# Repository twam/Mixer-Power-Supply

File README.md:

Mixer-Power-Supply
===

This repository is part of the USB audio mixer project described on https://www.twam.info/general/building-a-custom-usb-audio-mixer.

## License

[![CC BY-SA 4.0][cc-by-sa-shield]][cc-by-sa]

This work is licensed under a [Creative Commons Attribution-NonCommercial-ShareAlike 4.0 International License][cc-by-sa].

[![CC BY-SA 4.0][cc-by-sa-image]][cc-by-sa]

[cc-by-sa]: http://creativecommons.org/licenses/by-nc-sa/4.0/
[cc-by-sa-image]: https://licensebuttons.net/l/by-nc-sa/4.0/88x31.png
[cc-by-sa-shield]: https://img.shields.io/badge/License-CC%20BY--NC--SA%204.0-lightgrey.svg

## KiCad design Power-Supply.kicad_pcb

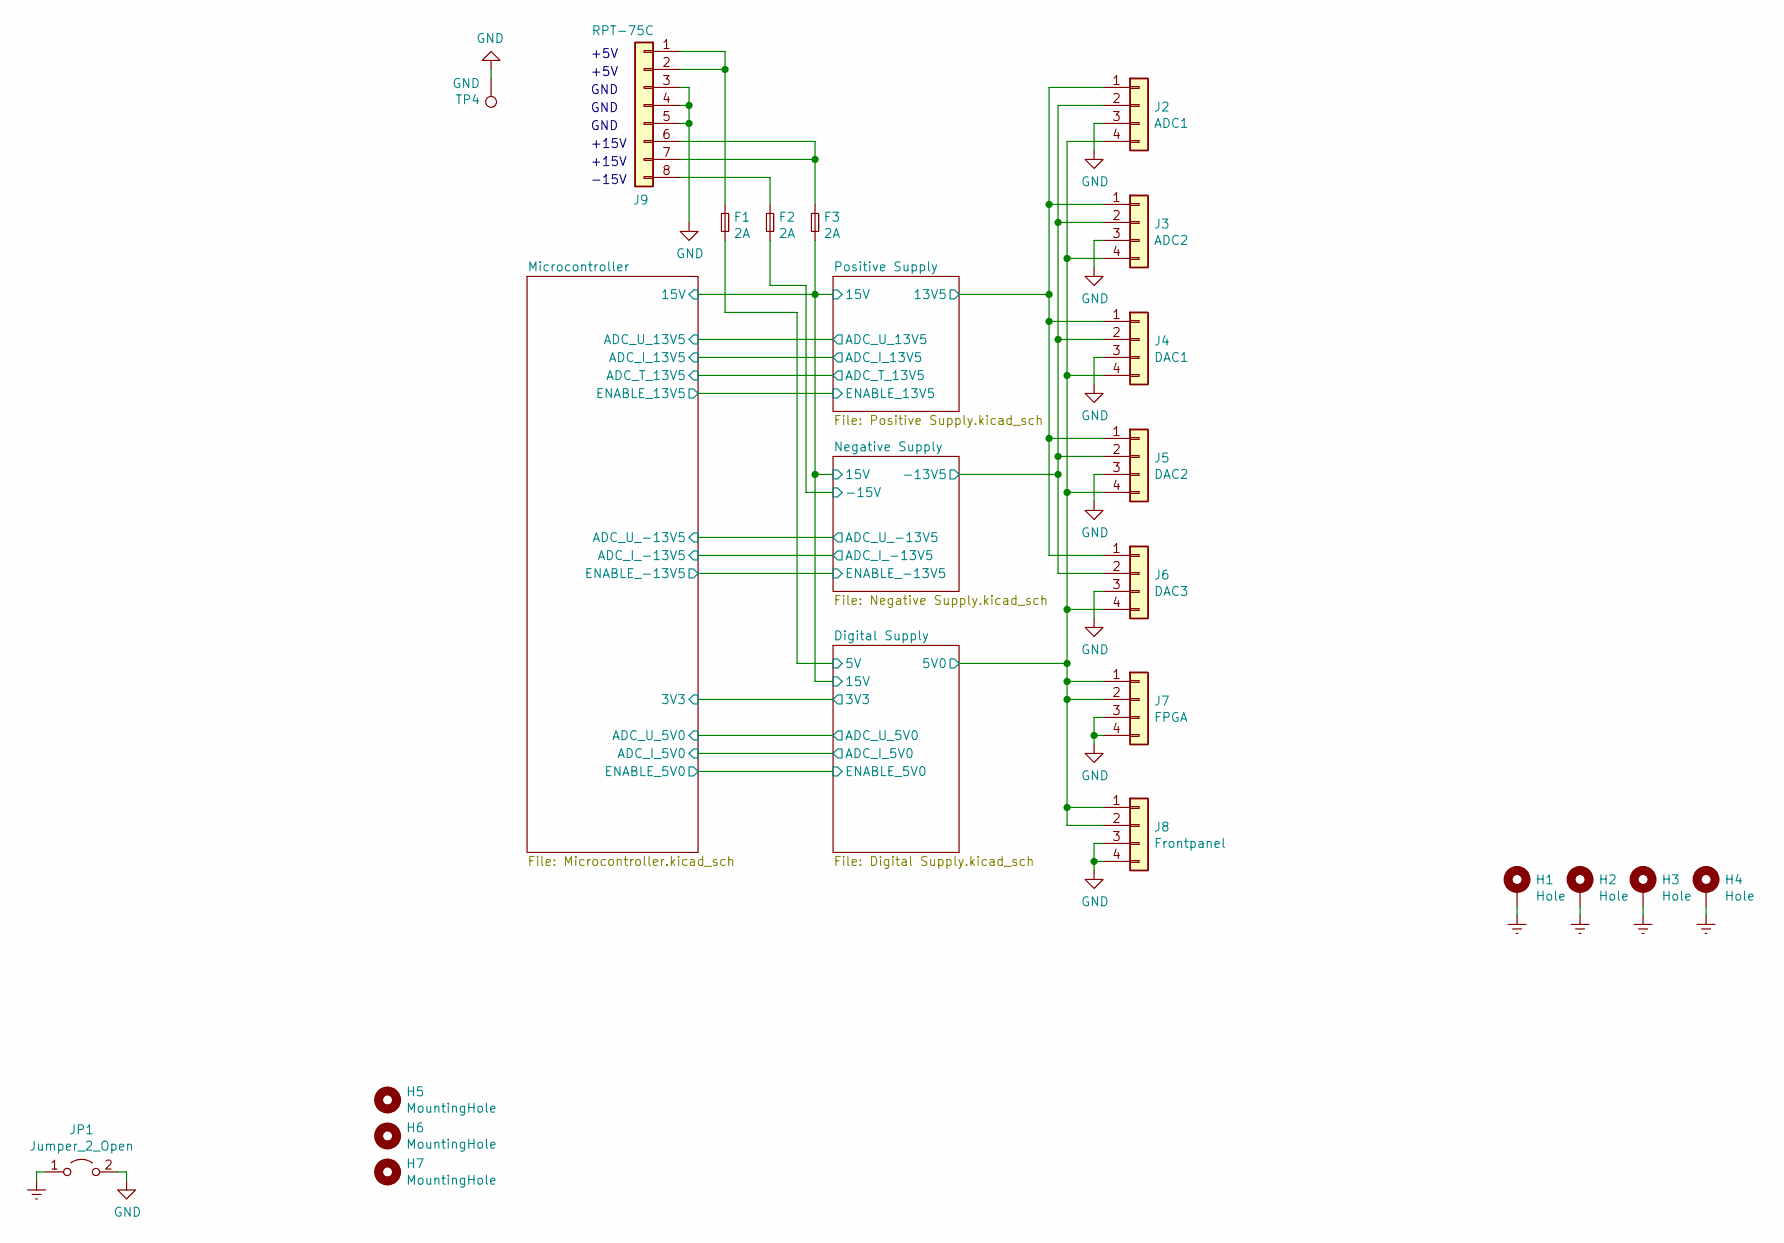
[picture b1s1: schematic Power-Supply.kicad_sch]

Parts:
F1, F2, F3: 2A; Fuse_0603_1608Metric_Pad1.05x0.95mm_HandSolder; LCSC C187605
H1, H2, H3, H4: Hole; MountingHole_3.2mm_M3_DIN965_Pad
H5, H6, H7: MountingHole; MountingHole_JLCPCB
J2: ADC1; JST_VH_B4P-VH_1x04_P3.96mm_Vertical
J3: ADC2; JST_VH_B4P-VH_1x04_P3.96mm_Vertical
J4: DAC1; JST_VH_B4P-VH_1x04_P3.96mm_Vertical
J5: DAC2; JST_VH_B4P-VH_1x04_P3.96mm_Vertical
J6: DAC3; JST_VH_B4P-VH_1x04_P3.96mm_Vertical
J7: FPGA; JST_VH_B4P-VH_1x04_P3.96mm_Vertical
J8: Frontpanel; JST_VH_B4P-VH_1x04_P3.96mm_Vertical
J9: RPT-75C; JST_VH_B8P-VH_1x08_P3.96mm_Vertical
JP1: Jumper_2_Open; SolderJumper-2_P1.3mm_Open_RoundedPad1.0x1.5mm
TP4: GND; TestPoint_Pad_D2.0mm

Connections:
/Digital Supply/5V: F1.1; also elsewhere on the board
/Digital Supply/5V0: J2.4, J3.4, J4.4, J5.4, J6.4, J7.1, J7.2, J8.1, J8.2; also elsewhere on the board
/Digital Supply/15V: F3.1; also elsewhere on the board
/Negative Supply/-13V5: J2.2, J3.2, J4.2, J5.2, J6.2; also elsewhere on the board
/Negative Supply/-15V: F2.1; also elsewhere on the board
/Positive Supply/13V5: J2.1, J3.1, J4.1, J5.1, J6.1; also elsewhere on the board
Earth: H1.1, H2.1, H3.1, H4.1, JP1.1 (A)
GND: J2.3, J3.3, J4.3, J5.3, J6.3, J7.3, J7.4, J8.3, J8.4, J9.3, J9.4, J9.5, JP1.2 (B), TP4.1; also elsewhere on the board
unnamed: F1.2, J9.1, J9.2
unnamed: F2.2, J9.8
unnamed: F3.2, J9.6, J9.7

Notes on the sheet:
+5V
GND
-15V
+15V

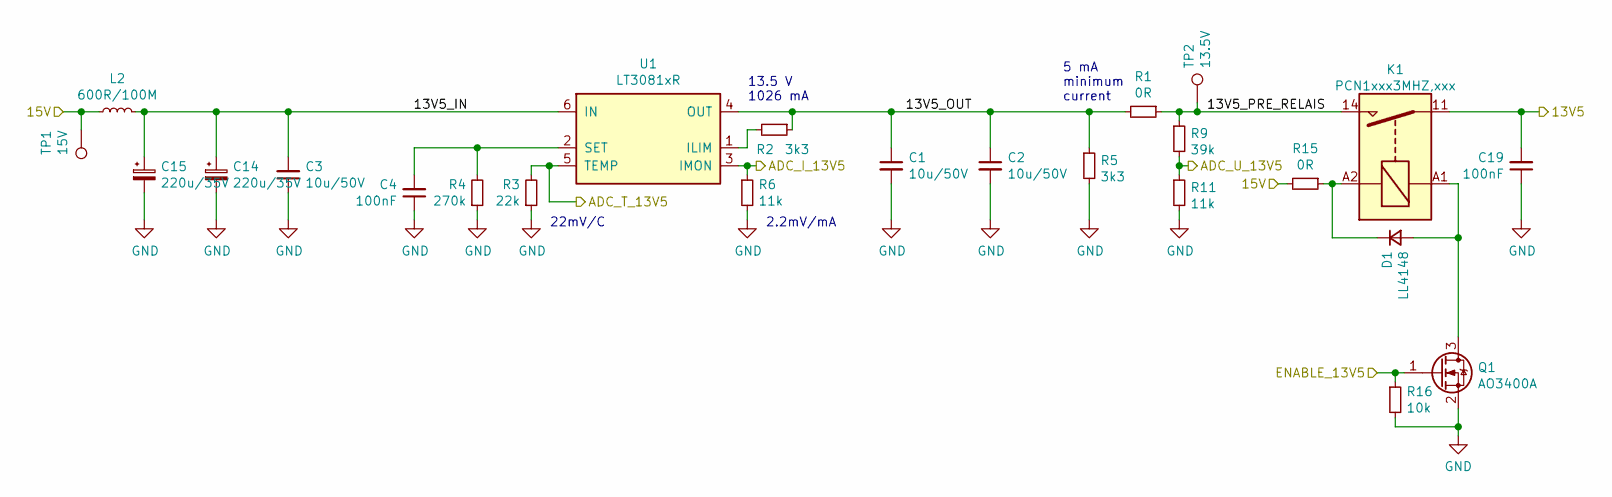
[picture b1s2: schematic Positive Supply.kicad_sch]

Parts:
C1, C2, C3: 10u/50V; C_1206_3216Metric; LCSC C13585
C4, C19: 100nF; C_0805_2012Metric; LCSC C49678
C14, C15: 220u/35V; CP_Radial_D8.0mm_P3.50mm; LCSC C201212
D1: LL4148; D_MiniMELF; LCSC C9808
K1: PCN1xxx3MHZ,xxx
L2: 600R/100M; L_0805_2012Metric; LCSC C1017
Q1: AO3400A; TSOT-23; LCSC C20917
R1, R15: 0R; R_0805_2012Metric; LCSC C17477
R2, R5: 3k3; R_0805_2012Metric; LCSC C26010
R3: 22k; R_0805_2012Metric; LCSC C17560
R4: 270k; R_0805_2012Metric; LCSC C17589
R6, R11: 11k; R_0805_2012Metric; LCSC C17429
R9: 39k; R_0805_2012Metric; LCSC C25826
R16: 10k; R_0805_2012Metric; LCSC C17414
TP1: 15V; TestPoint_Pad_D2.0mm
TP2: 13.5V; TestPoint_Pad_D2.0mm
U1: LT3081xR; TO-220-7_P2.54x3.8mm_StaggerOdd_Lead5.85mm_TabDown

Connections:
/Digital Supply/15V: L2.1, R15.2, TP1.1; also elsewhere on the board
/Microcontroller/ADC_I_13V5: R6.1, U1.3 (IMON); also elsewhere on the board
/Microcontroller/ADC_T_13V5: R3.2, U1.5 (TEMP); also elsewhere on the board
/Microcontroller/ADC_U_13V5: R9.2, R11.1; also elsewhere on the board
/Microcontroller/ENABLE_13V5: Q1.1 (G), R16.1; also elsewhere on the board
/Positive Supply/13V5: C19.2, K1.11; also elsewhere on the board
/Positive Supply/13V5_IN: C3.2, C14.1, C15.1, L2.2, U1.6 (IN)
/Positive Supply/13V5_OUT: C1.1, C2.1, R1.2, R2.1, R5.1, U1.4 (OUT)
/Positive Supply/13V5_PRE_RELAIS: K1.14, R1.1, R9.1, TP2.1
GND: C1.2, C2.2, C3.1, C4.1, C14.2, C15.2, C19.1, Q1.2 (S), R3.1, R4.1, R5.2, R6.2, R11.2, R16.2; also elsewhere on the board
unnamed: C4.2, R4.2, U1.2 (SET)
unnamed: D1.1 (K), K1.A2, R15.1
unnamed: D1.2 (A), K1.A1, Q1.3 (D)
unnamed: R2.2, U1.1 (ILIM)

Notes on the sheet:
2.2mV/mA
5 mA minimum current
22mV/C
13.5 V 1026 mA

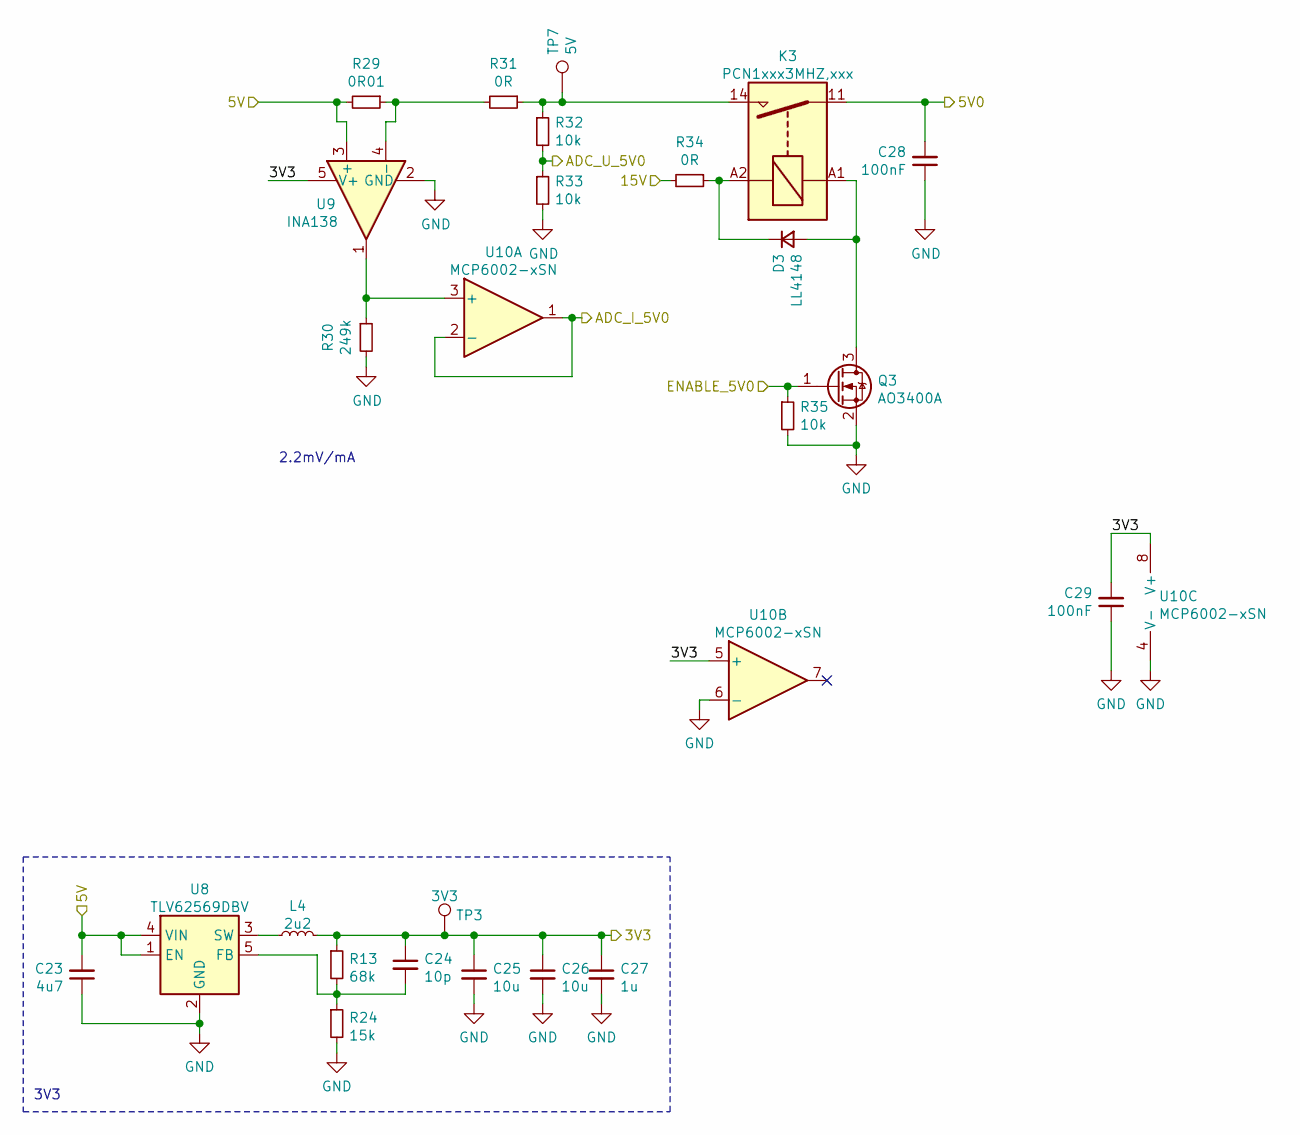
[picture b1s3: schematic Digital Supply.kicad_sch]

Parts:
C23: 4u7; C_0805_2012Metric; LCSC C1779
C24: 10p; C_0805_2012Metric; LCSC C1785
C25, C26: 10u; C_0805_2012Metric; LCSC C15850
C27: 1u; C_0805_2012Metric; LCSC C28323
C28, C29: 100nF; C_0805_2012Metric; LCSC C49678
D3: LL4148; D_MiniMELF; LCSC C9808
K3: PCN1xxx3MHZ,xxx
L4: 2u2; L_0805_2012Metric; LCSC C216156
Q3: AO3400A; TSOT-23; LCSC C20917
R13: 68k; R_0805_2012Metric; LCSC C17801
R24: 15k; R_0805_2012Metric; LCSC C17475
R29: 0R01; R_1206_3216Metric; LCSC C308574
R30: 249k; R_0805_2012Metric; LCSC C25825
R31, R34: 0R; R_0805_2012Metric; LCSC C17477
R32, R33, R35: 10k; R_0805_2012Metric; LCSC C17414
TP3: 3V3; TestPoint_Pad_D1.5mm
TP7: 5V; TestPoint_Pad_D2.0mm
U8: TLV62569DBV; SOT-23-5; LCSC C141836
U9: INA138; SOT-23-5; LCSC C47914
U10: MCP6002-xSN; SOIC-8_3.9x4.9mm_P1.27mm

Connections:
/Digital Supply/3V3: C24.1, C25.1, C26.1, C27.1, C29.2, L4.2, R13.1, TP3.1, U9.5 (V+), U10.5 (+), U10.8 (V+); also elsewhere on the board
/Digital Supply/5V: C23.2, R29.2, U8.1 (EN), U8.4 (VIN), U9.3 (+); also elsewhere on the board
/Digital Supply/5V0: C28.2, K3.11; also elsewhere on the board
/Digital Supply/15V: R34.2; also elsewhere on the board
/Digital Supply/ADC_I_5V0: U10.1, U10.2 (-); also elsewhere on the board
/Digital Supply/ADC_U_5V0: R32.2, R33.1; also elsewhere on the board
/Digital Supply/ENABLE_5V0: Q3.1 (G), R35.1; also elsewhere on the board
GND: C23.1, C25.2, C26.2, C27.2, C28.1, C29.1, Q3.2 (S), R24.2, R30.2, R33.2, R35.2, U8.2 (GND), U9.2 (GND), U10.4 (V-), U10.6 (-); also elsewhere on the board
unnamed: C24.2, R13.2, R24.1, U8.5 (FB)
unnamed: D3.1 (K), K3.A2, R34.1
unnamed: D3.2 (A), K3.A1, Q3.3 (D)
unnamed: K3.14, R31.1, R32.1, TP7.1
unnamed: L4.1, U8.3 (SW)
unnamed: R29.1, R31.2, U9.4 (-)
unnamed: R30.1, U9.1, U10.3 (+)

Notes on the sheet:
2.2mV/mA
3V3

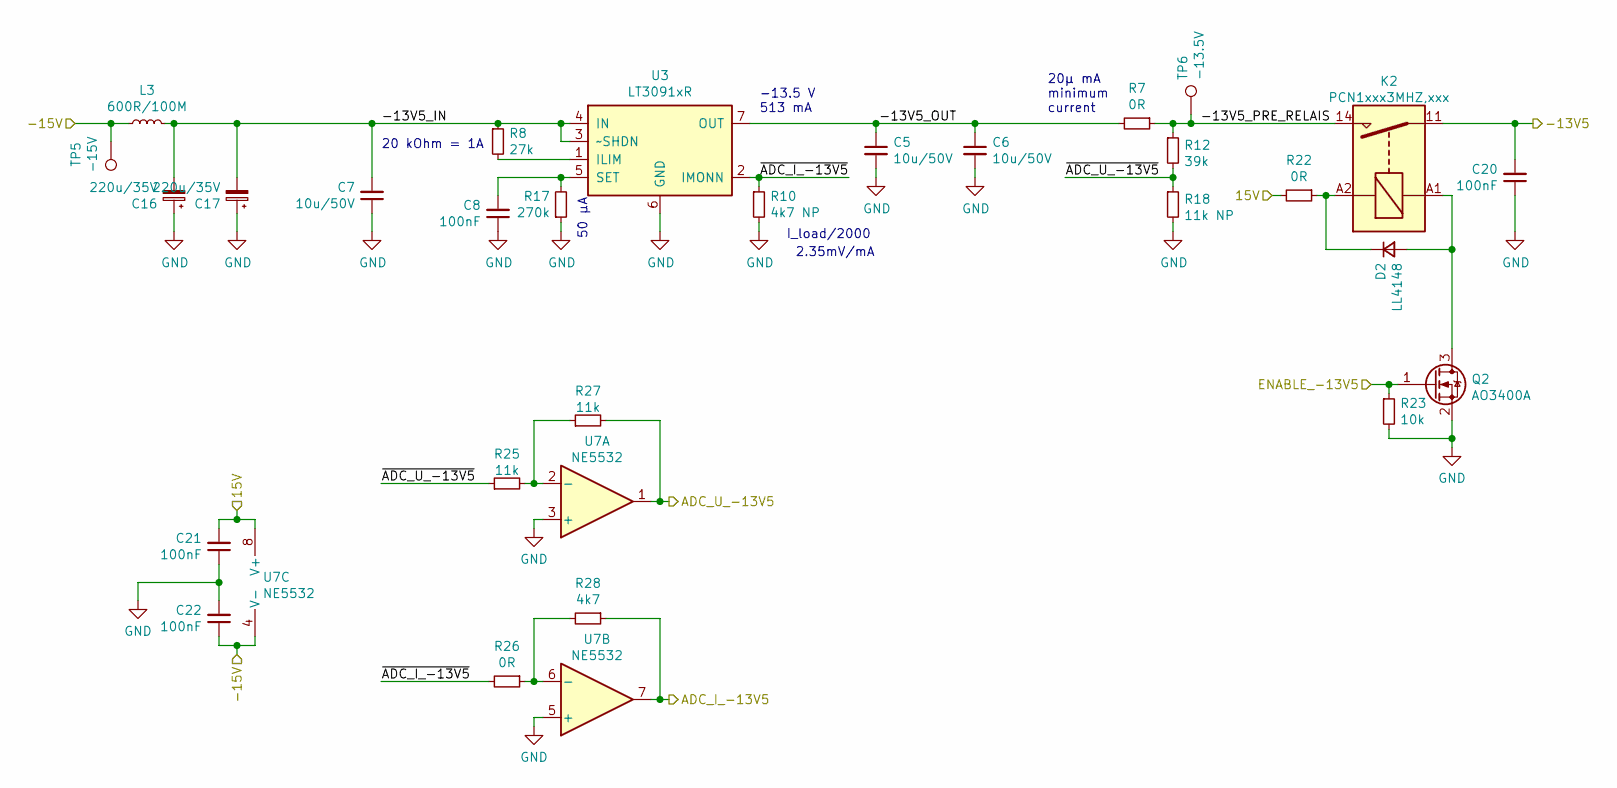
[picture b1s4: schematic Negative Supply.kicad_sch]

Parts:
C5, C6, C7: 10u/50V; C_1206_3216Metric; LCSC C13585
C8, C20, C21, C22: 100nF; C_0805_2012Metric; LCSC C49678
C16, C17: 220u/35V; CP_Radial_D8.0mm_P3.50mm; LCSC C201212
D2: LL4148; D_MiniMELF; LCSC C9808
K2: PCN1xxx3MHZ,xxx
L3: 600R/100M; L_0805_2012Metric; LCSC C1017
Q2: AO3400A; TSOT-23; LCSC C20917
R7, R22, R26: 0R; R_0805_2012Metric; LCSC C17477
R8: 27k; R_0805_2012Metric; LCSC C26010
R10: 4k7 NP; R_0805_2012Metric; LCSC C17673
R12: 39k; R_0805_2012Metric; LCSC C25826
R17: 270k; R_0805_2012Metric; LCSC C17589
R18: 11k NP; R_0805_2012Metric
R23: 10k; R_0805_2012Metric; LCSC C17414
R25, R27: 11k; R_0805_2012Metric; LCSC C17429
R28: 4k7; R_0805_2012Metric; LCSC C17673
TP5: -15V; TestPoint_Pad_D2.0mm
TP6: -13.5V; TestPoint_Pad_D2.0mm
U3: LT3091xR; TO-220-7_P2.54x3.8mm_StaggerOdd_Lead5.85mm_TabDown
U7: NE5532; SOIC-8_3.9x4.9mm_P1.27mm

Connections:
/Digital Supply/15V: C21.2, R22.2, U7.8 (V+); also elsewhere on the board
/Microcontroller/ADC_I_-13V5: R28.1, U7.7; also elsewhere on the board
/Microcontroller/ADC_U_-13V5: R27.2, U7.1; also elsewhere on the board
/Microcontroller/ENABLE_-13V5: Q2.1 (G), R23.1; also elsewhere on the board
/Negative Supply/-13V5: C20.2, K2.11; also elsewhere on the board
/Negative Supply/-13V5_IN: C7.2, C16.2, C17.2, L3.2, R8.1, U3.3 (~SHDN), U3.4 (IN)
/Negative Supply/-13V5_OUT: C5.1, C6.1, R7.2, U3.7 (OUT)
/Negative Supply/-13V5_PRE_RELAIS: K2.14, R7.1, R12.1, TP6.1
/Negative Supply/-15V: C22.1, L3.1, TP5.1, U7.4 (V-); also elsewhere on the board
/Negative Supply/~ADC_I_-13V5: R10.1, R26.2, U3.2 (IMONN)
/Negative Supply/~ADC_U_-13V5: R12.2, R18.1, R25.1
GND: C5.2, C6.2, C7.1, C8.1, C16.1, C17.1, C20.1, C21.1, C22.2, Q2.2 (S), R10.2, R17.1, R18.2, R23.2, U3.6 (GND), U7.3 (+), U7.5 (+); also elsewhere on the board
unnamed: C8.2, R17.2, U3.5 (SET)
unnamed: D2.1 (K), K2.A2, R22.1
unnamed: D2.2 (A), K2.A1, Q2.3 (D)
unnamed: R8.2, U3.1 (ILIM)
unnamed: R25.2, R27.1, U7.2 (-)
unnamed: R26.1, R28.2, U7.6 (-)

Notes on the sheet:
20µ mA minimum current
20 kOhm = 1A
I_load/2000
50 µA
2.35mV/mA
-13.5 V 513 mA

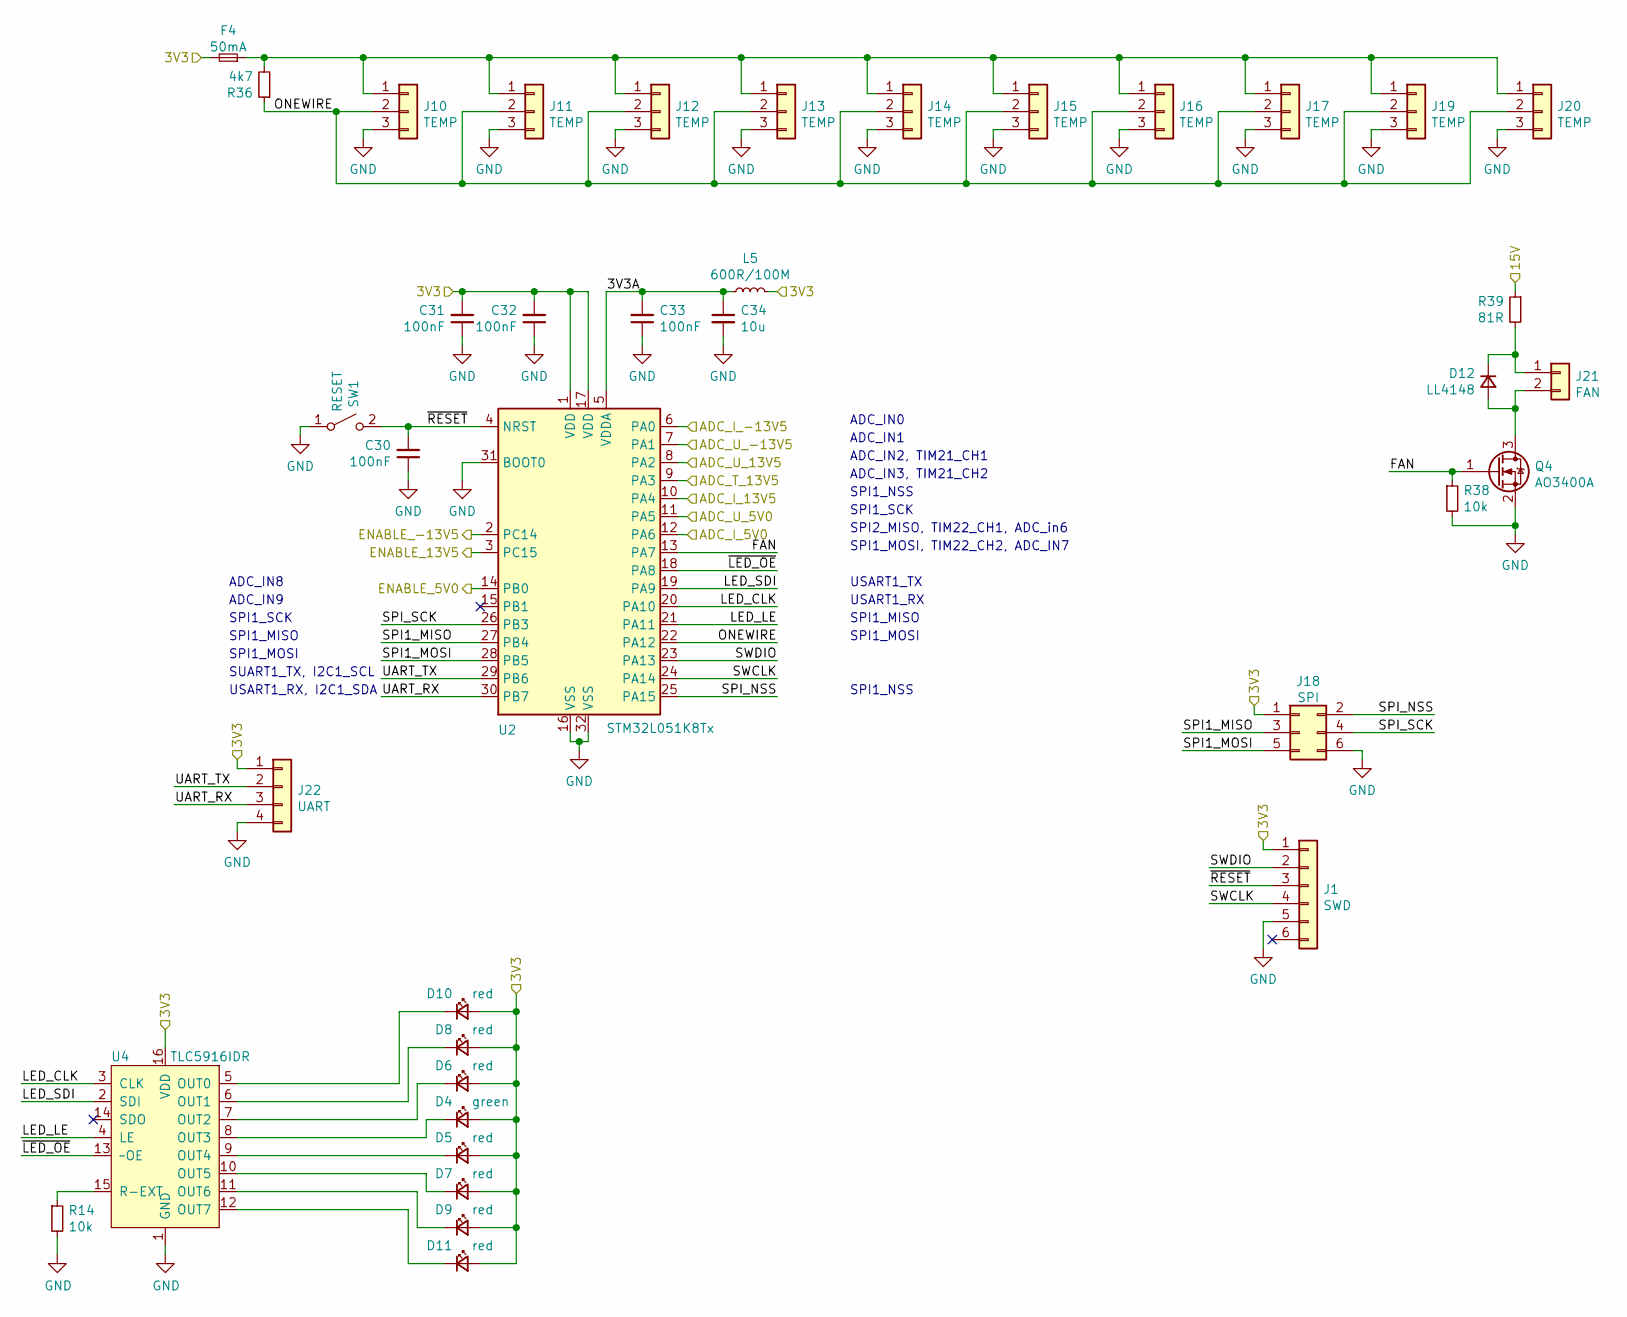
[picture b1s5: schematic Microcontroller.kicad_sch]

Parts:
C30, C31, C32, C33: 100nF; C_0603_1608Metric; LCSC C14663
C34: 10u; C_0805_2012Metric; LCSC C15850
D4: green; LED_0805_2012Metric; LCSC C2297
D5, D6, D7, D8, D9, D10, D11: red; LED_0805_2012Metric; LCSC C84256
D12: LL4148; D_MiniMELF; LCSC C9808
F4: 50mA; Fuse_0603_1608Metric_Pad1.05x0.95mm_HandSolder
J1: SWD; Tag-Connect_TC2030-IDC-NL_2x03_P1.27mm_Vertical
J10, J11, J12, J13, J14, J15, J16, J17, J19, J20: TEMP; Molex_KK-254_AE-6410-03A_1x03_P2.54mm_Vertical
J18: SPI; PinHeader_2x03_P2.54mm_Vertical
J21: FAN; Molex_KK-254_AE-6410-02A_1x02_P2.54mm_Vertical
J22: UART; PinHeader_1x04_P2.54mm_Vertical
L5: 600R/100M; L_0805_2012Metric; LCSC C1017
Q4: AO3400A; TSOT-23; LCSC C20917
R14, R38: 10k; R_0805_2012Metric; LCSC C17414
R36: 4k7; R_0805_2012Metric; LCSC C17673
R39: 81R; R_0805_2012Metric; LCSC C17819
SW1: RESET; SW_SPST_B3U-1000P; LCSC C231329
U2: STM32L051K8Tx; LQFP-32_7x7mm_P0.8mm
U4: TLC5916IDR; SOIC-16_3.9x9.9mm_P1.27mm; LCSC C90107

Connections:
/Digital Supply/3V3: C31.2, C32.2, D4.2 (A), D5.2 (A), D6.2 (A), D7.2 (A), D8.2 (A), D9.2 (A), D10.2 (A), D11.2 (A), F4.2, J1.1, J18.1, J22.1, L5.2, U2.1 (VDD), U2.17 (VDD), U4.16 (VDD); also elsewhere on the board
/Digital Supply/15V: R39.1; also elsewhere on the board
/Digital Supply/ADC_I_5V0: U2.12 (PA6); also elsewhere on the board
/Digital Supply/ADC_U_5V0: U2.11 (PA5); also elsewhere on the board
/Digital Supply/ENABLE_5V0: U2.14 (PB0); also elsewhere on the board
/Microcontroller/3V3A: C33.2, C34.1, L5.1, U2.5 (VDDA)
/Microcontroller/ADC_I_13V5: U2.10 (PA4); also elsewhere on the board
/Microcontroller/ADC_I_-13V5: U2.6 (PA0); also elsewhere on the board
/Microcontroller/ADC_T_13V5: U2.9 (PA3); also elsewhere on the board
/Microcontroller/ADC_U_13V5: U2.8 (PA2); also elsewhere on the board
/Microcontroller/ADC_U_-13V5: U2.7 (PA1); also elsewhere on the board
/Microcontroller/ENABLE_13V5: U2.3 (PC15); also elsewhere on the board
/Microcontroller/ENABLE_-13V5: U2.2 (PC14); also elsewhere on the board
/Microcontroller/FAN: Q4.1 (G), R38.1, U2.13 (PA7)
/Microcontroller/LED_CLK: U2.20 (PA10), U4.3 (CLK)
/Microcontroller/LED_LE: U2.21 (PA11), U4.4 (LE)
/Microcontroller/LED_SDI: U2.19 (PA9), U4.2 (SDI)
/Microcontroller/ONEWIRE: J10.2, J11.2, J12.2, J13.2, J14.2, J15.2, J16.2, J17.2, J19.2, J20.2, R36.1, U2.22 (PA12)
/Microcontroller/SPI1_MISO: J18.3, U2.27 (PB4)
/Microcontroller/SPI1_MOSI: J18.5, U2.28 (PB5)
/Microcontroller/SPI_NSS: J18.2, U2.25 (PA15)
/Microcontroller/SPI_SCK: J18.4, U2.26 (PB3)
/Microcontroller/SWCLK: J1.4, U2.24 (PA14)
/Microcontroller/SWDIO: J1.2, U2.23 (PA13)
/Microcontroller/UART_RX: J22.3, U2.30 (PB7)
/Microcontroller/UART_TX: J22.2, U2.29 (PB6)
/Microcontroller/~LED_OE: U2.18 (PA8), U4.13 (~OE)
/Microcontroller/~RESET: C30.2, J1.3, SW1.2 (B), U2.4 (NRST)
GND: C30.1, C31.1, C32.1, C33.1, C34.2, J1.5, J10.3, J11.3, J12.3, J13.3, J14.3, J15.3, J16.3, J17.3, J18.6, J19.3, J20.3, J22.4, Q4.2 (S), R14.2, R38.2, SW1.1 (A), U2.16 (VSS), U2.31 (BOOT0), U2.32 (VSS), U4.1 (GND); also elsewhere on the board
unnamed: D4.1 (K), U4.8 (OUT3)
unnamed: D5.1 (K), U4.9 (OUT4)
unnamed: D6.1 (K), U4.7 (OUT2)
unnamed: D7.1 (K), U4.10 (OUT5)
unnamed: D8.1 (K), U4.6 (OUT1)
unnamed: D9.1 (K), U4.11 (OUT6)
unnamed: D10.1 (K), U4.5 (OUT0)
unnamed: D11.1 (K), U4.12 (OUT7)
unnamed: D12.1 (K), J21.1, R39.2
unnamed: D12.2 (A), J21.2, Q4.3 (D)
unnamed: F4.1, J10.1, J11.1, J12.1, J13.1, J14.1, J15.1, J16.1, J17.1, J19.1, J20.1, R36.2
unnamed: R14.1, U4.15 (R-EXT)

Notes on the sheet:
USART1_RX, I2C1_SDA
SPI1_MISO
SPI1_SCK
SPI1_MOSI
SPI1_MISO
SPI1_NSS
USART1_RX
SPI2_MISO, TIM22_CH1, ADC_in6
ADC_IN3, TIM21_CH2
SPI1_MOSI, TIM22_CH2, ADC_IN7
ADC_IN0
SUART1_TX, I2C1_SCL
ADC_IN9
ADC_IN8
ADC_IN2, TIM21_CH1
USART1_TX
ADC_IN1

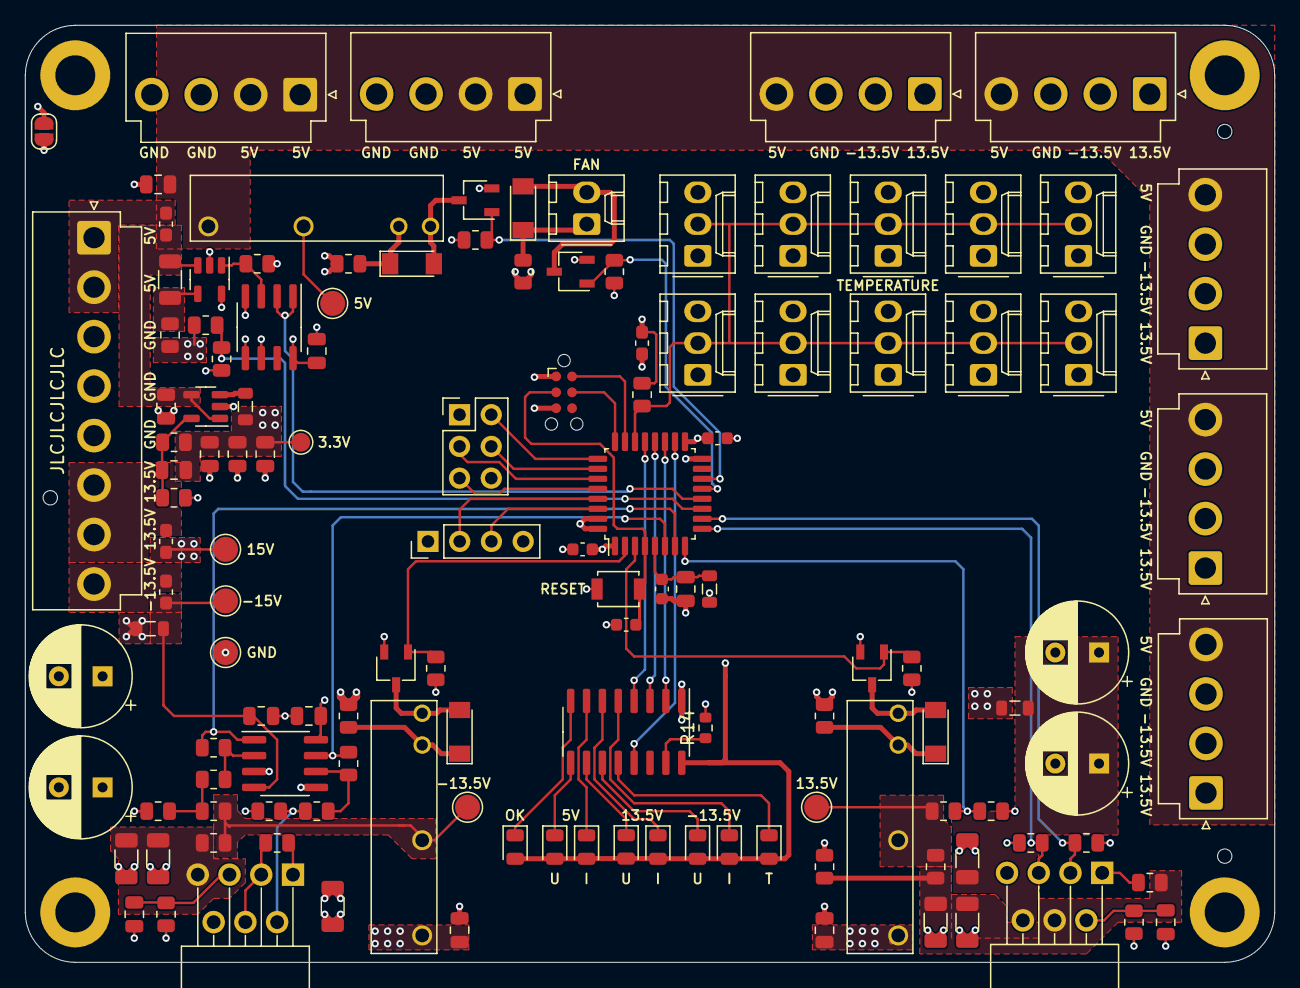
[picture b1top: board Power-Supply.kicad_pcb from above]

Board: 4 copper layers, 100.0 x 75.0 mm, 136 parts (0 on the bottom side), 75 nets.

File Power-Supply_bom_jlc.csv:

"Comment","Designator","Footprint","LCSC Part #"
"10u/50V","C1,C2,C3,C5,C6,C7","C_1206_3216Metric","C13585"
"100nF","C4,C19,C8,C20,C21,C22,C28,C29","C_0805_2012Metric","C49678"
"220u/35V","C14,C15,C16,C17","CP_Radial_D8.0mm_P3.50mm","C201212"
"4u7","C23","C_0805_2012Metric","C1779"
"10p","C24","C_0805_2012Metric","C1785"
"10u","C25,C26,C34","C_0805_2012Metric","C15850"
"1u","C27","C_0805_2012Metric","C28323"
"100nF","C30,C31,C32,C33","C_0603_1608Metric","C14663"
"LL4148","D1,D2,D3,D12","D_MiniMELF","C9808"
"green","D4","LED_0805_2012Metric","C2297"
"red","D5,D6,D7,D8,D9,D10,D11","LED_0805_2012Metric","C84256"
"2A","F1,F2,F3","Fuse_0603_1608Metric_Pad1.05x0.95mm_HandSolder","C187605"
"600R/100M","L2,L3,L5","L_0805_2012Metric","C1017"
"2u2","L4","L_0805_2012Metric","C216156"
"AO3400A","Q1,Q2,Q3,Q4","TSOT-23","C20917"
"0R","R1,R15,R7,R22,R26,R31,R34","R_0805_2012Metric","C17477"
"2k","R2","R_0805_2012Metric","C17604"
"22k","R3","R_0805_2012Metric","C17560"
"270k","R4,R17","R_0805_2012Metric","C17589"
"3k3","R5","R_0805_2012Metric","C26010"
"11k","R6,R11,R18,R25,R27","R_0805_2012Metric","C17429"
"39k","R9,R8,R12","R_0805_2012Metric","C25826"
"4k7","R10","R_0805_2012Metric","C17673"
"68k","R13","R_0805_2012Metric","C17801"
"470R","R14","R_0805_2012Metric","C17709"
"10k","R16,R23,R28,R32,R33,R35,R36,R38","R_0805_2012Metric","C17414"
"15k","R24","R_0805_2012Metric","C17475"
"0R01","R29","R_1206_3216Metric","C308574"
"249k","R30","R_0805_2012Metric","C25825"
"81R","R39","R_0805_2012Metric","C17819"
"RESET","SW1","SW_SPST_B3U-1000P","C231329"
"TLC5916IDR","U4","SOIC-16_3.9x9.9mm_P1.27mm","C90107"
"NE5532","U7","SOIC-8_3.9x4.9mm_P1.27mm","C7426"
"TLV62569DBV","U8","SOT-23-5","C141836"
"INA138","U9","SOT-23-5","C47914"
"MCP6002-xSN","U10","SOIC-8_3.9x4.9mm_P1.27mm","C7377"

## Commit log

2021-06-05 Initial commit. Rev 2
2022-01-07 Update Gerbers and add JLCPCB position/BOM files
2022-01-07 Update to KiCad 6
2022-01-15 Add README
